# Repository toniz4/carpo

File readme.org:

#+BEGIN_HTML html
<picture align="center">
  <source media="(prefers-color-scheme: dark)" srcset="/assets/carpo_logo_dark.svg">
  <source media="(prefers-color-scheme: light)" srcset="/assets/carpo_logo_light.svg">
  
</picture>
#+END_HTML

Carpo is a 36 keys, low profile, choc spaced, split keyboard. Based on the Holyiot 18010 BLE module.

It features kailh choc v1 switches, a 200mah battery, status led and a thin and sleek case.

#+BEGIN_HTML html

<details>
<summary>More photos</summary>

<p>The case is printed in JLCPCB using the 8001 resin</p>
<p>The keycaps are Pseudoku's Chicago Stenographer, printed in JLCPCB using the JLC black resin.</p>

<h2>PCB renders</h2>

</details>
#+END_HTML

The blue status LED will blink showing the Bluetooth status, if it's breathing it's disconnected. After connecting, it will blink a number of times, corresponding to the index of the current Bluetooth profile (profile 0 will blink 1 time, profile 1, 2 times, etc.)

** PCB

The PCB gerbers are in [[./pcb/gerbers/left_gerber.zip]] and [[./pcb/gerbers/right_gerber.zip]]

*** BOM

This is the BOM for a single side, duplicate the quantity for both sides.

|------------+------------------------+-----+----------+------------|
| Reference  | Value                  | Qty | LCSC     | Aliexpress |
|------------+------------------------+-----+----------+------------|
| C1         | 1nF                    |   1 | C1588    | [[https://www.aliexpress.com/item/32966526545.html?algo_pvid=08497bf7-8a86-407a-8b8e-3f2fb615a087&algo_exp_id=08497bf7-8a86-407a-8b8e-3f2fb615a087-0&pdp_npi=4@dis!BRL!8.00!8.00!!!9.57!9.57!@2101ec1a17321645816996477ec6cf!66569661168!sea!BR!4340077984!X&curPageLogUid=dDSupVaq6MIe&utparam-url=scene:search%7Cquery_from:&gatewayAdapt=glo2bra][link]]       |
| C4,C5      | 4.7uF                  |   2 | C19666   | [[https://www.aliexpress.com/item/32966526545.html?spm=a2g0o.productlist.main.1.35542a88o0hyRD&algo_pvid=08497bf7-8a86-407a-8b8e-3f2fb615a087&algo_exp_id=08497bf7-8a86-407a-8b8e-3f2fb615a087-0&pdp_npi=4%40dis%21BRL%218.00%218.00%21%21%219.57%219.57%21%402101ec1a17321645816996477ec6cf%2166569661168%21sea%21BR%214340077984%21X&curPageLogUid=dDSupVaq6MIe&utparam-url=scene%3Asearch%7Cquery_from%3A][link]]       |
| C6,C7      | 1uF                    |   2 | C1592    | [[https://www.aliexpress.com/item/32966526545.html?spm=a2g0o.productlist.main.1.35542a88o0hyRD&algo_pvid=08497bf7-8a86-407a-8b8e-3f2fb615a087&algo_exp_id=08497bf7-8a86-407a-8b8e-3f2fb615a087-0&pdp_npi=4%40dis%21BRL%218.00%218.00%21%21%219.57%219.57%21%402101ec1a17321645816996477ec6cf%2166569661168%21sea%21BR%214340077984%21X&curPageLogUid=dDSupVaq6MIe&utparam-url=scene%3Asearch%7Cquery_from%3A][link]]       |
| D1...D18   | 1N4148                 |  18 | C909967  | [[https://www.aliexpress.com/item/32849879904.html?pdp_npi=4%40dis%21BRL%21R%24%2010%2C09%21R%24%2010%2C09%21%21%211.66%211.66%21%402103241117319619888525440e8871%2165195962302%21sh%21BR%214340077984%21X&spm=a2g0o.store_pc_allItems_or_groupList.new_all_items_2007523355393.32849879904][link]]       |
| D19        | 1N5819W                |   1 | C169540  | [[https://www.aliexpress.com/item/32849879904.html?pdp_npi=4%40dis%21BRL%21R%24%2010%2C09%21R%24%2010%2C09%21%21%211.66%211.66%21%402103241117319619888525440e8871%2165195962302%21sh%21BR%214340077984%21X&spm=a2g0o.store_pc_allItems_or_groupList.new_all_items_2007523355393.32849879904][link]]       |
| D20        | RED                    |   1 | C2286    | [[https://www.aliexpress.com/item/1005005981379885.html?spm=a2g0o.productlist.main.1.7b99DxRPDxRPdx&algo_pvid=18eb9153-bacb-4ca3-8257-d5c9a437a83b&algo_exp_id=18eb9153-bacb-4ca3-8257-d5c9a437a83b-0&pdp_npi=4%40dis%21BRL%217.01%214.66%21%21%218.39%215.58%21%402103246617321624426335786e6bb7%2112000035165361804%21sea%21BR%214340077984%21X&curPageLogUid=PSjrLVZGbaW6&utparam-url=scene%3Asearch%7Cquery_from%3A][link]]       |
| D21        | Blue                   |   1 | C72041   | [[https://www.aliexpress.com/item/1005005981379885.html?spm=a2g0o.productlist.main.1.7b99DxRPDxRPdx&algo_pvid=18eb9153-bacb-4ca3-8257-d5c9a437a83b&algo_exp_id=18eb9153-bacb-4ca3-8257-d5c9a437a83b-0&pdp_npi=4%40dis%21BRL%217.01%214.66%21%21%218.39%215.58%21%402103246617321624426335786e6bb7%2112000035165361804%21sea%21BR%214340077984%21X&curPageLogUid=PSjrLVZGbaW6&utparam-url=scene%3Asearch%7Cquery_from%3A][link]]       |
| ESD1       | USBLC6-2P6             |   1 | C3647099 | [[https://www.aliexpress.com/item/1005006444169732.html?spm=a2g0o.productlist.main.1.781b3a44TLrw2m&algo_pvid=40c8f6aa-c9c2-4348-b44f-925523ad9abe&algo_exp_id=40c8f6aa-c9c2-4348-b44f-925523ad9abe-0&pdp_npi=4%40dis%21BRL%2118.80%2116.73%21%21%2122.40%2119.94%21%402103011017319617929641965e5f47%2112000037187648433%21sea%21BR%214340077984%21X&curPageLogUid=ZOsaWC8jlKBv&utparam-url=scene%3Asearch%7Cquery_from%3A][link]]       |
| F1         | 500mA                  |   1 | C269104  | [[https://www.aliexpress.com/item/1005005611093145.html?pdp_npi=4%40dis%21BRL%21R%24%209%2C00%21R%24%209%2C00%21%21%211.48%211.48%21%402101e9a217319675854382731e3c4c%2112000033743292567%21sh%21BR%214340077984%21X&spm=a2g0o.store_pc_allItems_or_groupList.new_all_items_2007523355393.1005005611093145][link]]       |
| J1         | USB_C_Receptacle       |   1 | C168688  | [[https://www.aliexpress.com/item/1005006344850545.html?spm=a2g0o.productlist.main.5.173559f9Ugh9y4&algo_pvid=3a6d0134-a4b9-42d0-b8a4-66ebb8356b63&algo_exp_id=3a6d0134-a4b9-42d0-b8a4-66ebb8356b63-2&pdp_npi=4%40dis%21BRL%2124.49%218.81%21%21%2129.23%2110.52%21%402103205217320632751638596e8ef7%2112000036833801400%21sea%21BR%214340077984%21X&curPageLogUid=W3n2Fg6B5rM8&utparam-url=scene%3Asearch%7Cquery_from%3A][link]]       |
| J2         | X1224WRS-02-LPV01      |   1 | C528028  | [[https://www.aliexpress.com/item/1005008059654298.html?spm=a2g0o.productlist.main.11.58513536xtKhKv&algo_pvid=bd3aa922-aa15-45c9-a93a-175bdb605849&algo_exp_id=bd3aa922-aa15-45c9-a93a-175bdb605849-5&pdp_npi=4%40dis%21BRL%2117.94%2117.94%21%21%212.95%212.95%21%402101e7f617319616422893688e9f23%2112000043491427239%21sea%21BR%214340077984%21X&curPageLogUid=7pDVXv2m4wOY&utparam-url=scene%3Asearch%7Cquery_from%3A][link]]       |
| Q1         | AO3401A                |   1 | C15127   | [[https://www.aliexpress.com/item/32491247912.html?pdp_npi=4%40dis%21BRL%21R%24%2010%2C86%21R%24%2010%2C86%21%21%211.79%211.79%21%402101fb0b17320483947675690e66e4%2112000021469328951%21sh%21BR%214340077984%21X&spm=a2g0o.store_pc_allItems_or_groupList.new_all_items_2007523355393.32491247912][link]]       |
| R1,R2      | 5.1K                   |   2 | C23186   | [[https://www.aliexpress.com/item/32847135098.html?pdp_npi=4%40dis%21BRL%21R%24%207%2C95%21R%24%207%2C95%21%21%211.31%211.31%21%4021030ea417320477566177655e9c92%2165168386237%21sh%21BR%214340077984%21X&spm=a2g0o.store_pc_allItems_or_groupList.new_all_items_2007523355393.32847135098][link]]       |
| R3         | 1M                     |   1 | C22935   | [[https://www.aliexpress.com/item/32847135098.html?pdp_npi=4%40dis%21BRL%21R%24%207%2C95%21R%24%207%2C95%21%21%211.31%211.31%21%4021030ea417320477566177655e9c92%2165168386237%21sh%21BR%214340077984%21X&spm=a2g0o.store_pc_allItems_or_groupList.new_all_items_2007523355393.32847135098][link]]       |
| R4         | 100k                   |   1 | C25803   | [[https://www.aliexpress.com/item/32847135098.html?pdp_npi=4%40dis%21BRL%21R%24%207%2C95%21R%24%207%2C95%21%21%211.31%211.31%21%4021030ea417320477566177655e9c92%2165168386237%21sh%21BR%214340077984%21X&spm=a2g0o.store_pc_allItems_or_groupList.new_all_items_2007523355393.32847135098][link]]       |
| R5,R9      | 1K                     |   2 | C21190   | [[https://www.aliexpress.com/item/32847135098.html?pdp_npi=4%40dis%21BRL%21R%24%207%2C95%21R%24%207%2C95%21%21%211.31%211.31%21%4021030ea417320477566177655e9c92%2165168386237%21sh%21BR%214340077984%21X&spm=a2g0o.store_pc_allItems_or_groupList.new_all_items_2007523355393.32847135098][link]]       |
| R6         | RPROG*                 |   1 | C22978   | [[https://www.aliexpress.com/item/32847135098.html?pdp_npi=4%40dis%21BRL%21R%24%207%2C95%21R%24%207%2C95%21%21%211.31%211.31%21%4021030ea417320477566177655e9c92%2165168386237%21sh%21BR%214340077984%21X&spm=a2g0o.store_pc_allItems_or_groupList.new_all_items_2007523355393.32847135098][link]]       |
| R7         | 806/820k               |   1 | C103828  | [[https://www.aliexpress.com/item/1005005180820900.html?spm=a2g0o.productlist.main.1.6134qFKhqFKhPF&algo_pvid=969d0013-7308-43b2-93d5-d0302bfc5325&algo_exp_id=969d0013-7308-43b2-93d5-d0302bfc5325-0&pdp_npi=4%40dis%21BRL%2111.17%2111.17%21%21%2113.33%2113.33%21%402101effb17320481852814788ebca1%2112000031996358565%21sea%21BR%214340077984%21X&curPageLogUid=E6k8bUI6WbVH&utparam-url=scene%3Asearch%7Cquery_from%3A][link]]       |
| R8         | 2M                     |   1 | C22976   | [[https://www.aliexpress.com/item/32847135098.html?pdp_npi=4%40dis%21BRL%21R%24%207%2C95%21R%24%207%2C95%21%21%211.31%211.31%21%4021030ea417320477566177655e9c92%2165168386237%21sh%21BR%214340077984%21X&spm=a2g0o.store_pc_allItems_or_groupList.new_all_items_2007523355393.32847135098][link]]       |
| R_TACT1    | SW_Push                |   1 | C79175   | [[https://www.aliexpress.com/item/1005005453787620.html?spm=a2g0o.productlist.main.1.11d71ae5j97qJo&algo_pvid=568eff6e-180e-4b37-958c-7c0a3b0f84d9&algo_exp_id=568eff6e-180e-4b37-958c-7c0a3b0f84d9-0&pdp_npi=4%40dis%21BRL%2110.94%219.89%21%21%2113.03%2111.78%21%402103273e17319427737965163e3c62%2112000038111003831%21sea%21BR%214340077984%21X&curPageLogUid=5a6rqzQqwGi2&utparam-url=scene%3Asearch%7Cquery_from%3A][link]]       |
| SW1...SW18 | SW_SPST                |  18 | NA       | [[https://www.aliexpress.com/item/1005004290562374.html?spm=a2g0o.order_list.order_list_main.11.1b7a1802tGxfP6][link]]       |
| SW19       | PCM12SMTR              |   1 | C221841  | [[https://www.aliexpress.com/item/4000685483225.html?spm=a2g0o.productlist.main.1.4da74032HBAqDQ&algo_pvid=10bd21db-ab70-499e-9712-915123677f21&algo_exp_id=10bd21db-ab70-499e-9712-915123677f21-0&pdp_npi=4%40dis%21BRL%2111.04%2111.04%21%21%211.82%211.82%21%402101efeb17320638433678674eb91b%2112000037044894568%21sea%21BR%214340077984%21X&curPageLogUid=D7VprpuG9aRi&utparam-url=scene%3Asearch%7Cquery_from%3A][link]]       |
| U1         | nRF52840_holyiot_18010 |   1 | NA       | [[https://www.aliexpress.com/item/32951888809.html?spm=a2g0o.productlist.main.3.7701b3f332egzL&algo_pvid=593cb489-4431-4b1e-9b7c-13da5fe36363&algo_exp_id=593cb489-4431-4b1e-9b7c-13da5fe36363-1&pdp_npi=4%40dis%21BRL%2166.29%2166.29%21%21%2110.93%2110.93%21%402101c80017320638597317082e5c7f%2166335833131%21sea%21BR%214340077984%21X&curPageLogUid=kvt9pjM1CKCY&utparam-url=scene%3Asearch%7Cquery_from%3A][link]]       |
| U2         | XC6206P332MR-G         |   1 | C5446    | [[https://www.aliexpress.com/item/1005005560879957.html?spm=a2g0o.productlist.main.1.8147565e8xPCNS&algo_pvid=832843ed-a07d-488e-9a95-02c42698494f&algo_exp_id=832843ed-a07d-488e-9a95-02c42698494f-0&pdp_npi=4%40dis%21BRL%218.31%218.31%21%21%211.37%211.37%21%40210313e917320639779521928ed48d%2112000033548906902%21sea%21BR%214340077984%21X&curPageLogUid=XQoBcdRpxlZc&utparam-url=scene%3Asearch%7Cquery_from%3A][link]]       |
| U3         | MCP73831               |   1 | C14879   | [[https://www.aliexpress.com/item/32714249253.html?spm=a2g0o.productlist.main.5.4e943cd6VJpTkW&algo_pvid=d1f289e1-092b-4c7f-a226-af7a4b6ba5b8&algo_exp_id=d1f289e1-092b-4c7f-a226-af7a4b6ba5b8-2&pdp_npi=4%40dis%21BRL%2111.61%2111.61%21%21%211.91%211.91%21%402103205117319429034655653e1f6e%2161012982711%21sea%21BR%214340077984%21X&curPageLogUid=2HwIj03rL6Cx&utparam-url=scene%3Asearch%7Cquery_from%3A][link]]       |
| NA         | 502025                 |   1 | NA       | [[https://www.aliexpress.com/item/1005007356459315.html?gatewayAdapt=glo2bra][link]]       |
| NA         | 781720002*             |   1 | NA       | [[https://www.aliexpress.com/item/1005004784691542.html?gatewayAdapt=glo2bra][link]]       |
|------------+------------------------+-----+----------+------------|

- RPROG: You can use 5.1K resistors already included for the USB-C. See schematic for RPROG values, keep it at max 500mA.
- 781720002: Buy the J003 option.

** Case

It's recommended to print in resin, printing in FDM printers was not tested.

Currently, some walls near the battery switch and reset are too thin, if you are printing with jlcpcb they may complain about that. I will fix this in a future version. But the result came out fine.

*** BOM
|--------------------------+----------+------------|
| Component                | Quantity | Aliexpress |
|--------------------------+----------+------------|
| M2 Countersunk screw 8mm |        8 | [[https://pt.aliexpress.com/item/32968368588.html?gatewayAdapt=glo2bra][link]]       |
| M2 Nut                   |        8 | [[https://pt.aliexpress.com/item/1005003121029934.html?gatewayAdapt=glo2bra][link]]       |
| 8x1.5mm Rubber Feet      |        8 | [[https://www.aliexpress.com/item/1005002620133214.html?spm=a2g0o.order_list.order_list_main.102.2ee8caa4V1HjrE&gatewayAdapt=glo2bra][link]]       |
| [[./case/top_left.stl][Left Top case]]            |        1 |            |
| [[./case/bottom_left.stl][Left Bottom case]]         |        1 |            |
| [[./case/top_right.stl][Right top case]]           |        1 |            |
| [[./case/bottom_right.stl][Right bottom case]]        |        1 |            |
|--------------------------+----------+------------|

** Building
*** PCB

The PCB is not easily hand solderable, I would recommend using a hotplate (I used [[https://pt.aliexpress.com/item/1005006380693061.html?gatewayAdapt=glo2bra][this]] one), or a rework station. Also some pads in the holyiot 18010 are not accessible for hand soldering.
Put solder paste in the pads and place the components. You can use as a reference the [[./pcb/left/bom/ibom.html][left ibom]] and [[./pcb/right/bom/ibom.html][right ibom]].
After that, ensure that there is no shorts.

*** Battery

To solder the cable included in the BOM to the battery, you can solder the cables directly to the battery cables, or unsolder the original battery cables, and solder the included cables to the battery.
*MAKE SURE TO NOT SHORT THE POSITIVE AND NEGATIVE LEADS, ESPECIALLY WHEN TRYING TO RUN THE CABLES WITH TWEEZERS TO THE SIDE OF THE BATTERY, DON'T ASK ME HOW I KNOW THIS*

** Firmware
*** Bootloader

Carpo uses the Adafruit nRF52 Bootloader. You can get it in this [[https://github.com/toniz4/Adafruit_nRF52_Bootloader][fork]]. The nrfmicro wiki
has a great section on flashing the bootloader, you can get it [[https://github.com/joric/nrfmicro/wiki/Bootloader][here]], but following the
build and flash sections of the Adafruit repo worked well for me. I used a rpi pico
flashed with [[https://github.com/raspberrypi/debugprobe][debugprobe]]. The SWD pins are accessible at the top of the PCB.

After flashing the bootloader, you should be able to double press the reset button to
enter in the bootloader mode, the blue status LED should breathe and it should appear as a
flash drive in your computer.

*** ZMK

The ZMK config can be found in this [[https://github.com/toniz4/zmk-config-carpo][repo]]. Just put the keyboard in bootloader mode, get the .uf2 firmware in the latest build [[https://github.com/toniz4/zmk-config-carpo/actions][artifact]], and copy the respective left and right .uf2 file to the left and right keyboard.

The layout is pretty barebones, so customize as you wish. In the ~personal~ branch I have the layout that I personally use.

** Credits and inspirations

It's thanks to various open source projects that I was able to make the Carpo keyboard.

- [[https://github.com/GEIGEIGEIST/TOTEM][TOTEM]]: Layout inspirations.
- [[https://github.com/yumagulovrn/dao-choc-ble?tab=readme-ov-file][Dao Choc BLE]]: Schematic design and PCB Layout.
- [[https://github.com/cacheworks/Wubbo][Wubbo]]: Schematic design.
- [[https://github.com/joric/nrfmicro][nRFMicro]] Schematic design and documentation, if it weren't for the nRFMicro documentation, this project wouldn't be possible.
- [[https://lowprokb.ca/products/corne-ish-zen][Corne-ish Zen]]: Case design and PCB Layout.

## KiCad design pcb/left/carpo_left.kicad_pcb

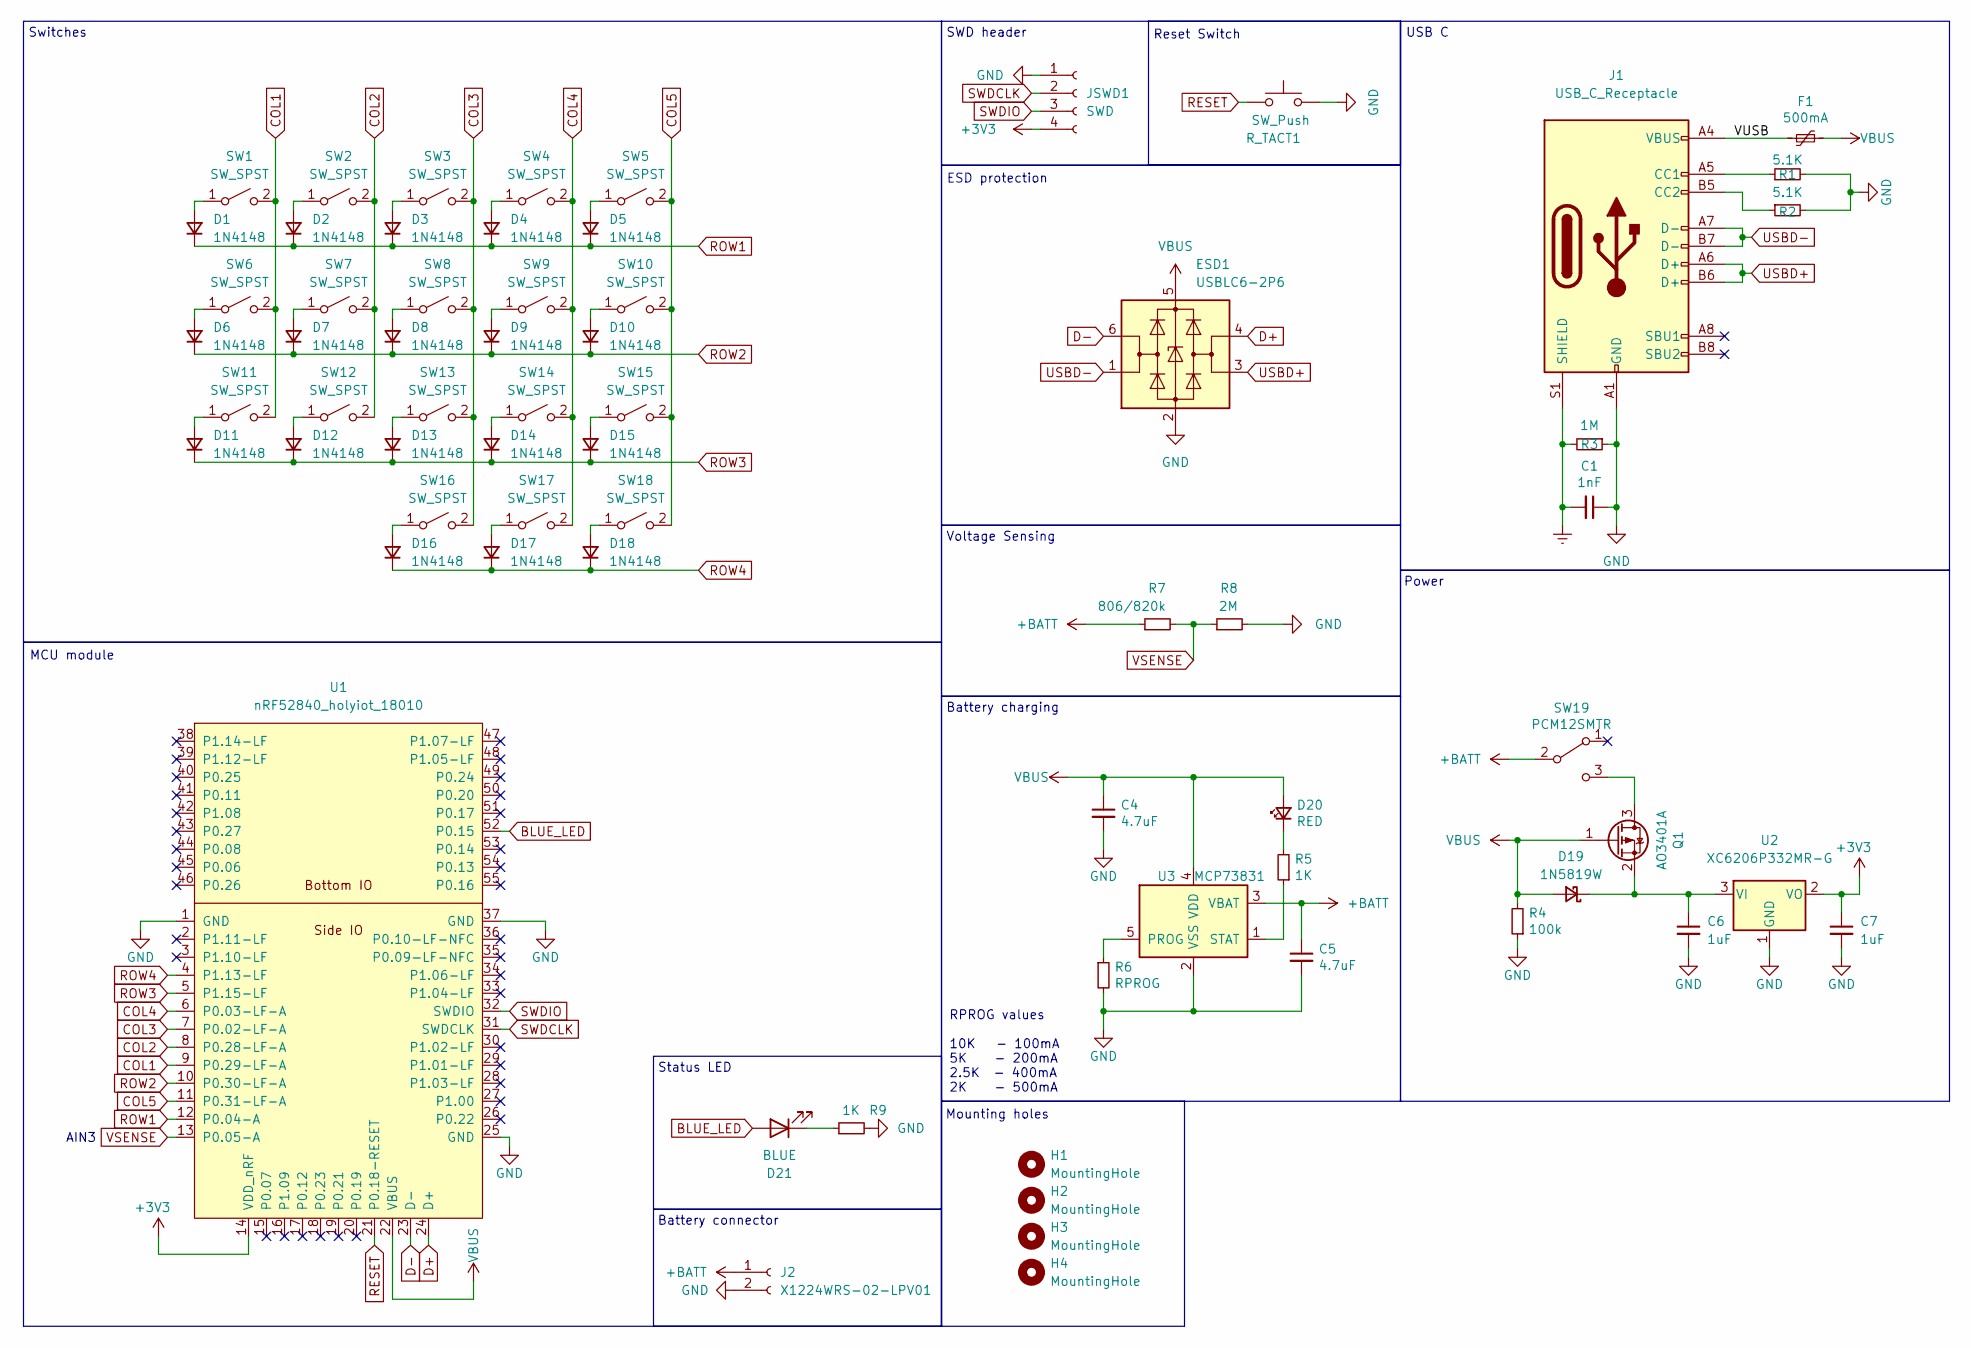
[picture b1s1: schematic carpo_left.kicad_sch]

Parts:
C1: 1nF; C_0603_1608Metric; LCSC C1588
C4, C5: 4.7uF; C_0603_1608Metric; LCSC C19666
C6, C7: 1uF; C_0603_1608Metric; LCSC C1592
D1, D2, D3, D4, D5, D6, D7, D8, D9, D10, D11, D12, D13, D14, D15, D16, D17, D18: 1N4148; D_SOD-123; LCSC C909967
D19: 1N5819W; D_SOD-123; LCSC C169540
D20: RED; LED_0603_1608Metric; LCSC C2286
D21: BLUE; LED_0603_1608Metric; LCSC C72041
ESD1: USBLC6-2P6; SOT-666; LCSC C3647099
F1: 500mA; Fuse_0805_2012Metric; LCSC C269104
H1, H2, H3, H4: MountingHole; StandoffHole_4.3mm
J1: USB_C_Receptacle; USB-C_C168688; LCSC C168688
J2: X1224WRS-02-LPV01; Molex_Pico-EZmate_78171-0002_1x02-1MP_P1.20mm_Vertical; LCSC C528028
JSWD1: SWD; Header_SWD
Q1: AO3401A; SOT-23; LCSC C15127
R1, R2: 5.1K; R_0603_1608Metric; LCSC C23186
R3: 1M; R_0603_1608Metric; LCSC C22935
R4: 100k; R_0603_1608Metric; LCSC C25803
R5, R9: 1K; R_0603_1608Metric; LCSC C21190
R6: RPROG; R_0603_1608Metric; LCSC C22978
R7: 806/820k; R_0603_1608Metric; LCSC C103828
R8: 2M; R_0603_1608Metric; LCSC C22976
R_TACT1: SW_Push; Panasonic_EVQPUL_EVQPUC; LCSC C79175
SW1, SW2, SW3, SW4, SW5, SW6, SW7, SW8, SW9, SW10, SW11, SW12, SW13, SW14, SW15, SW16, SW17: SW_SPST; SW_choc_v1_HS_CPG135001S30_1u
SW18: SW_SPST; SW_choc_v1_HS_CPG135001S30_1.5u
SW19: PCM12SMTR; SW_SPDT_PCM12; LCSC C221841
U1: nRF52840_holyiot_18010
U2: XC6206P332MR-G; SOT-23; LCSC C5446
U3: MCP73831; SOT-23-5; LCSC C14879

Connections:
+3V3: C7.1, JSWD1.4, U1.14 (VDD_nRF), U2.2 (VO)
+BATT: C5.1, J2.1, R7.1, SW19.2 (B), U3.3 (VBAT)
/VUSB: F1.2, J1.A4 (VBUS), J1.A9 (VBUS), J1.B4 (VBUS), J1.B9 (VBUS)
BLUE_LED: D21.2 (A), U1.52 (P0.15)
COL1: SW1.2 (B), SW6.2 (B), SW11.2 (B), U1.9 (P0.29-LF-A)
COL2: SW2.2 (B), SW7.2 (B), SW12.2 (B), U1.8 (P0.28-LF-A)
COL3: SW3.2 (B), SW8.2 (B), SW13.2 (B), SW16.2 (B), U1.7 (P0.02-LF-A)
COL4: SW4.2 (B), SW9.2 (B), SW14.2 (B), SW17.2 (B), U1.6 (P0.03-LF-A)
COL5: SW5.2 (B), SW10.2 (B), SW15.2 (B), SW18.2 (B), U1.11 (P0.31-LF-A)
D+: ESD1.4 (I/O2), U1.24 (D+)
D-: ESD1.6 (I/O1), U1.23 (D-)
Earth: C1.2, J1.S1 (SHIELD), R3.2
GND: C1.1, C4.2, C5.2, C6.2, C7.2, ESD1.2 (GND), J1.A1 (GND), J1.A12 (GND), J1.B1 (GND), J1.B12 (GND), J2.2, JSWD1.1, R1.2, R2.2, R3.1, R4.1, R6.2, R8.2, R9.2, R_TACT1.2, U1.1 (GND), U1.25 (GND), U1.37 (GND), U2.1 (GND), U3.2 (VSS)
unnamed: D1.2 (A), SW1.1 (A)
unnamed: D2.2 (A), SW2.1 (A)
unnamed: D3.2 (A), SW3.1 (A)
unnamed: D4.2 (A), SW4.1 (A)
unnamed: D5.2 (A), SW5.1 (A)
unnamed: D6.2 (A), SW6.1 (A)
unnamed: D7.2 (A), SW7.1 (A)
unnamed: D8.2 (A), SW8.1 (A)
unnamed: D9.2 (A), SW9.1 (A)
unnamed: D10.2 (A), SW10.1 (A)
unnamed: D11.2 (A), SW11.1 (A)
unnamed: D12.2 (A), SW12.1 (A)
unnamed: D13.2 (A), SW13.1 (A)
unnamed: D14.2 (A), SW14.1 (A)
unnamed: D15.2 (A), SW15.1 (A)
unnamed: D16.2 (A), SW16.1 (A)
unnamed: D17.2 (A), SW17.1 (A)
unnamed: D18.2 (A), SW18.1 (A)
unnamed: C6.1, D19.1 (K), Q1.2 (S), U2.3 (VI)
unnamed: D20.1 (K), R5.2
unnamed: D21.1 (K), R9.1
unnamed: J1.A5 (CC1), R1.1
unnamed: J1.B5 (CC2), R2.1
unnamed: Q1.3 (D), SW19.3 (C)
unnamed: R6.1, U3.5 (PROG)
unnamed: R5.1, U3.1 (STAT)
RESET: R_TACT1.1, U1.21 (P0.18-RESET)
ROW1: D1.1 (K), D2.1 (K), D3.1 (K), D4.1 (K), D5.1 (K), U1.12 (P0.04-A)
ROW2: D6.1 (K), D7.1 (K), D8.1 (K), D9.1 (K), D10.1 (K), U1.10 (P0.30-LF-A)
ROW3: D11.1 (K), D12.1 (K), D13.1 (K), D14.1 (K), D15.1 (K), U1.5 (P1.15-LF)
ROW4: D16.1 (K), D17.1 (K), D18.1 (K), U1.4 (P1.13-LF)
SWDCLK: JSWD1.2, U1.31 (SWDCLK)
SWDIO: JSWD1.3, U1.32 (SWDIO)
USBD+: ESD1.3 (I/O2), J1.A6 (D+), J1.B6 (D+)
USBD-: ESD1.1 (I/O1), J1.A7 (D-), J1.B7 (D-)
VBUS: C4.1, D19.2 (A), D20.2 (A), ESD1.5 (VBUS), F1.1, Q1.1 (G), R4.2, U1.22 (VBUS), U3.4 (VDD)
VSENSE: R7.2, R8.1, U1.13 (P0.05-A)

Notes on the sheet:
Battery charging
Power
RPROG values 10K - 100mA 5K - 200mA 2.5K - 400mA 2K - 500mA
Mounting holes
SWD header
AIN3
Switches
Voltage Sensing
USB C
Status LED
Battery connector
MCU module
Reset Switch
ESD protection

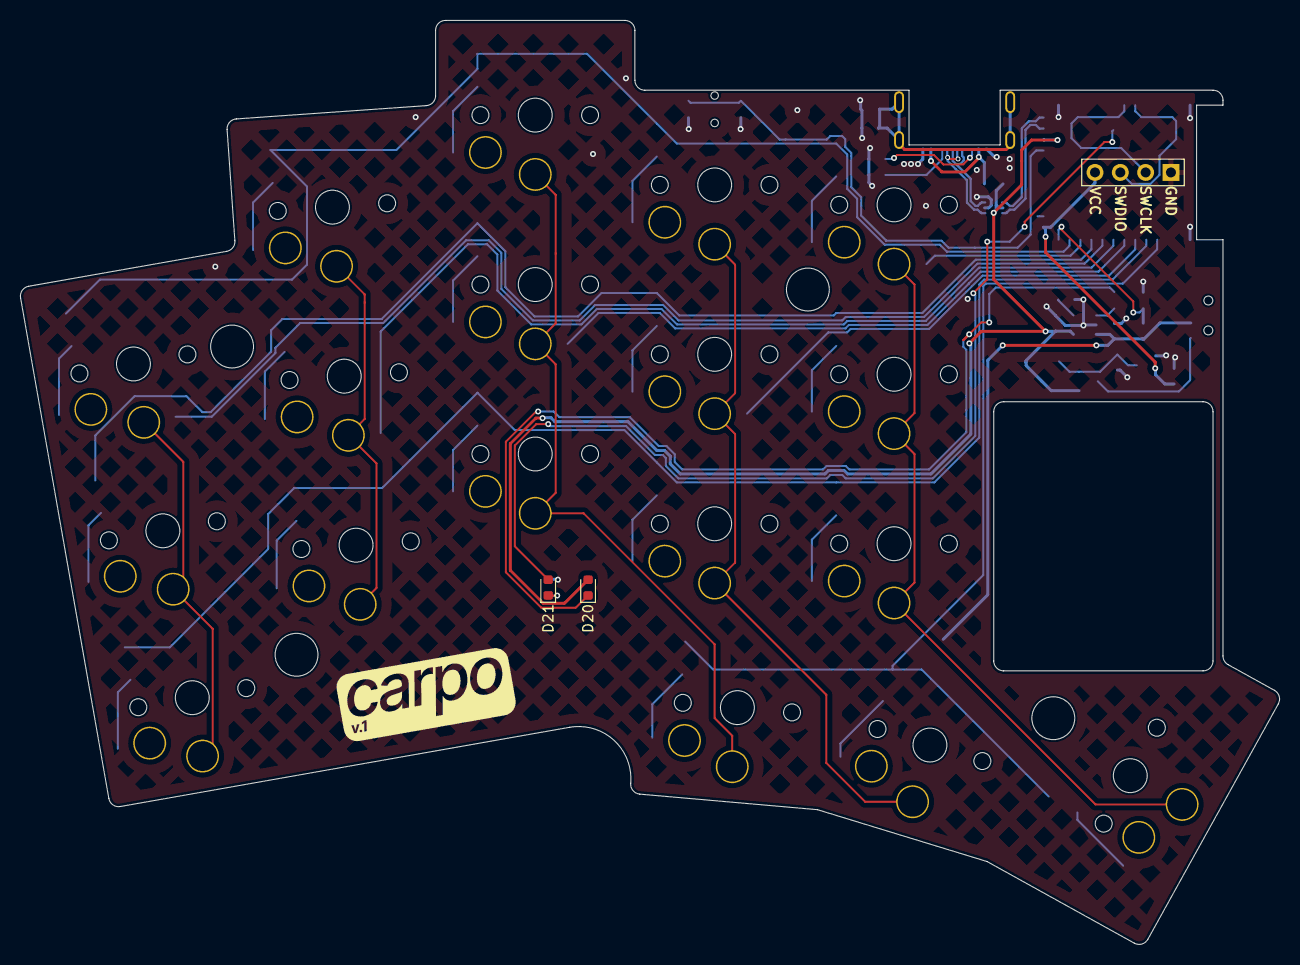
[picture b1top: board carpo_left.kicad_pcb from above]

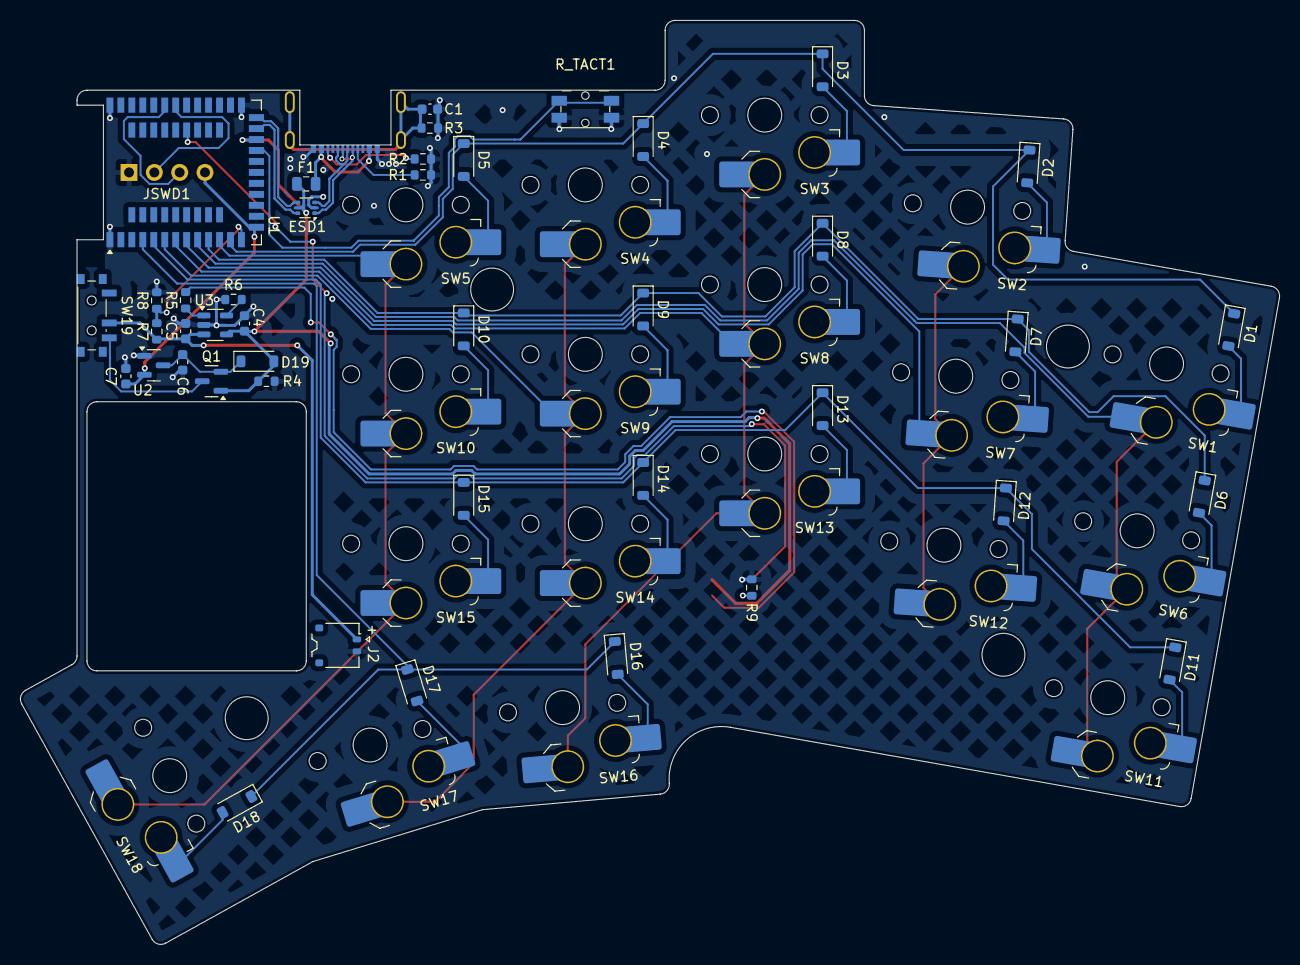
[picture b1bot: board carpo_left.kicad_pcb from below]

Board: 2 copper layers, 126.3 x 92.7 mm, 68 parts (61 on the bottom side), 50 nets.

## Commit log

2024-06-18 add left right
2024-12-20 latest carpo version
2024-12-21 readme changes
2024-12-23 add image
